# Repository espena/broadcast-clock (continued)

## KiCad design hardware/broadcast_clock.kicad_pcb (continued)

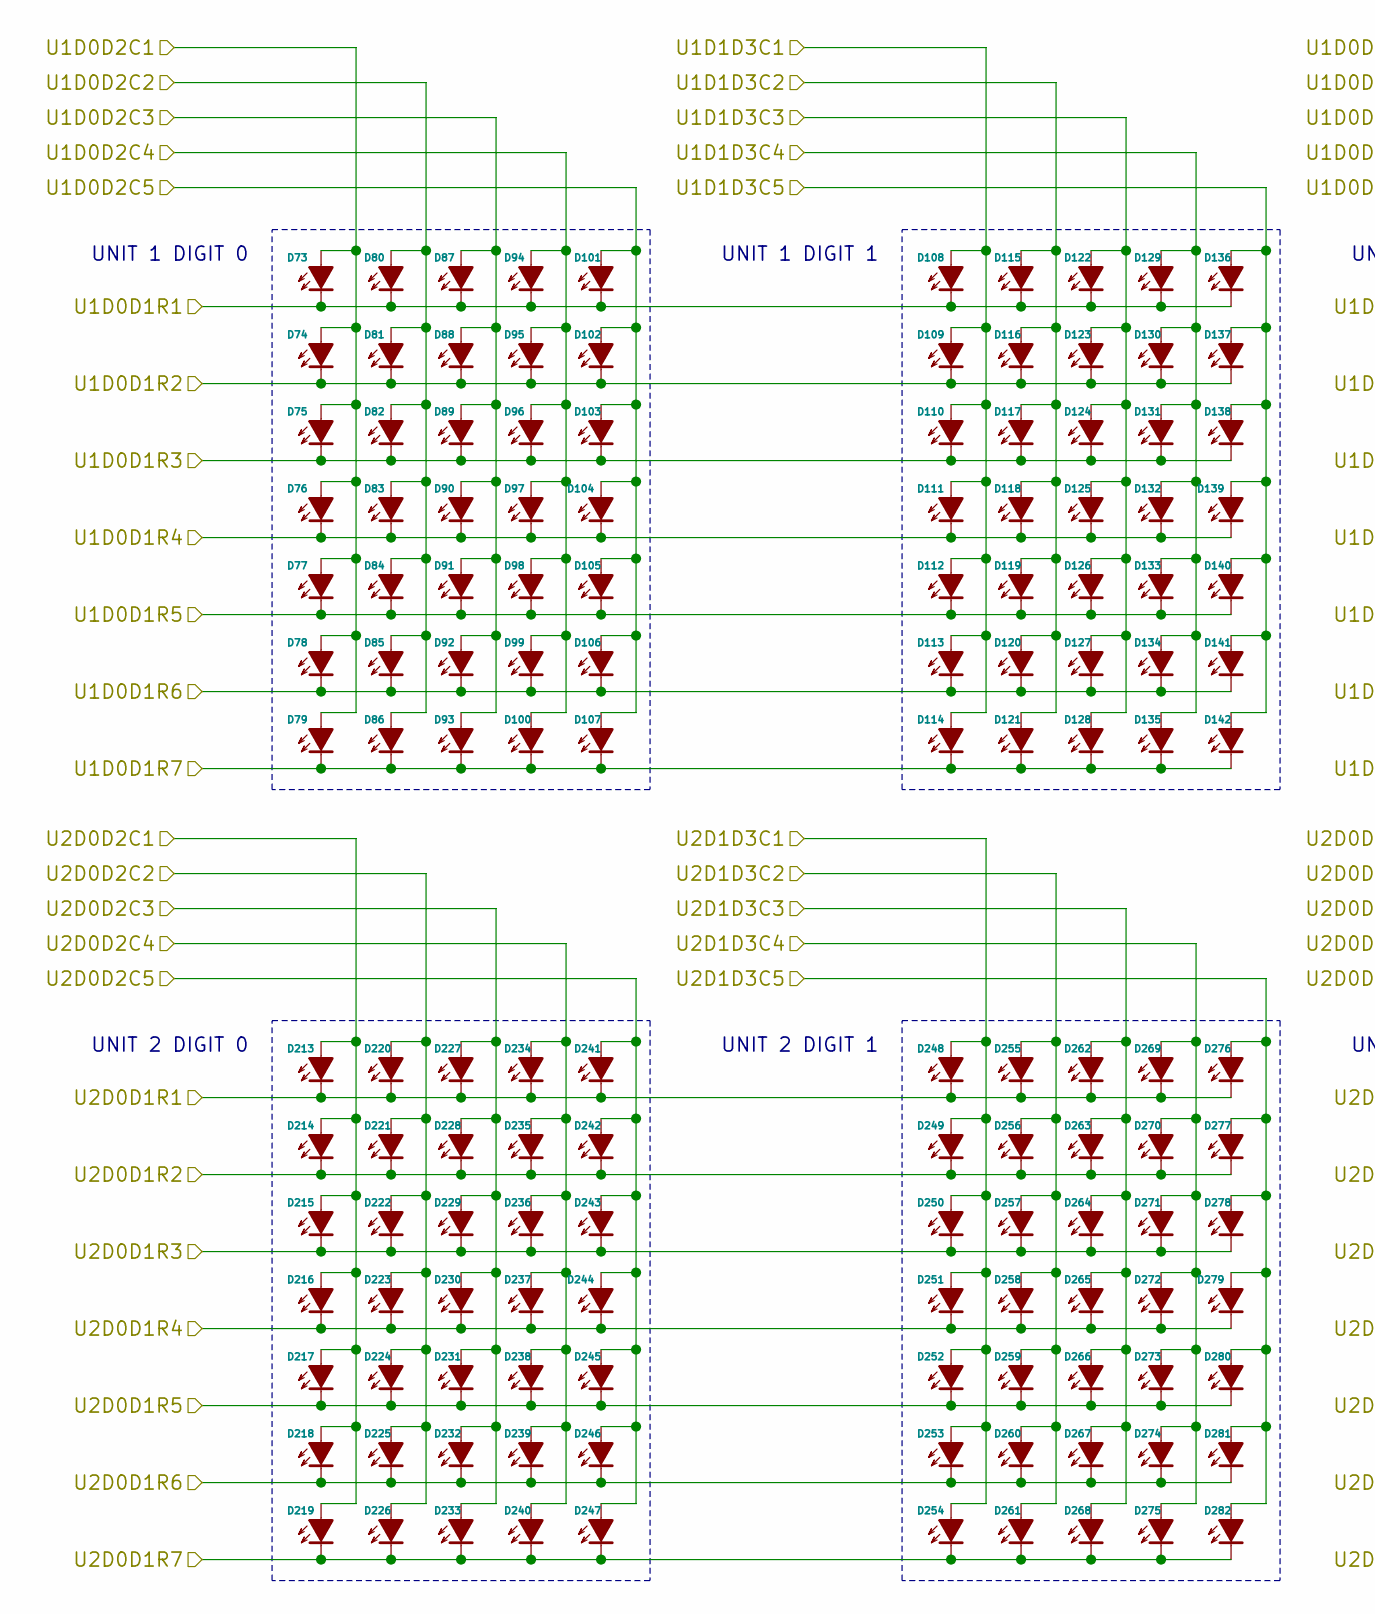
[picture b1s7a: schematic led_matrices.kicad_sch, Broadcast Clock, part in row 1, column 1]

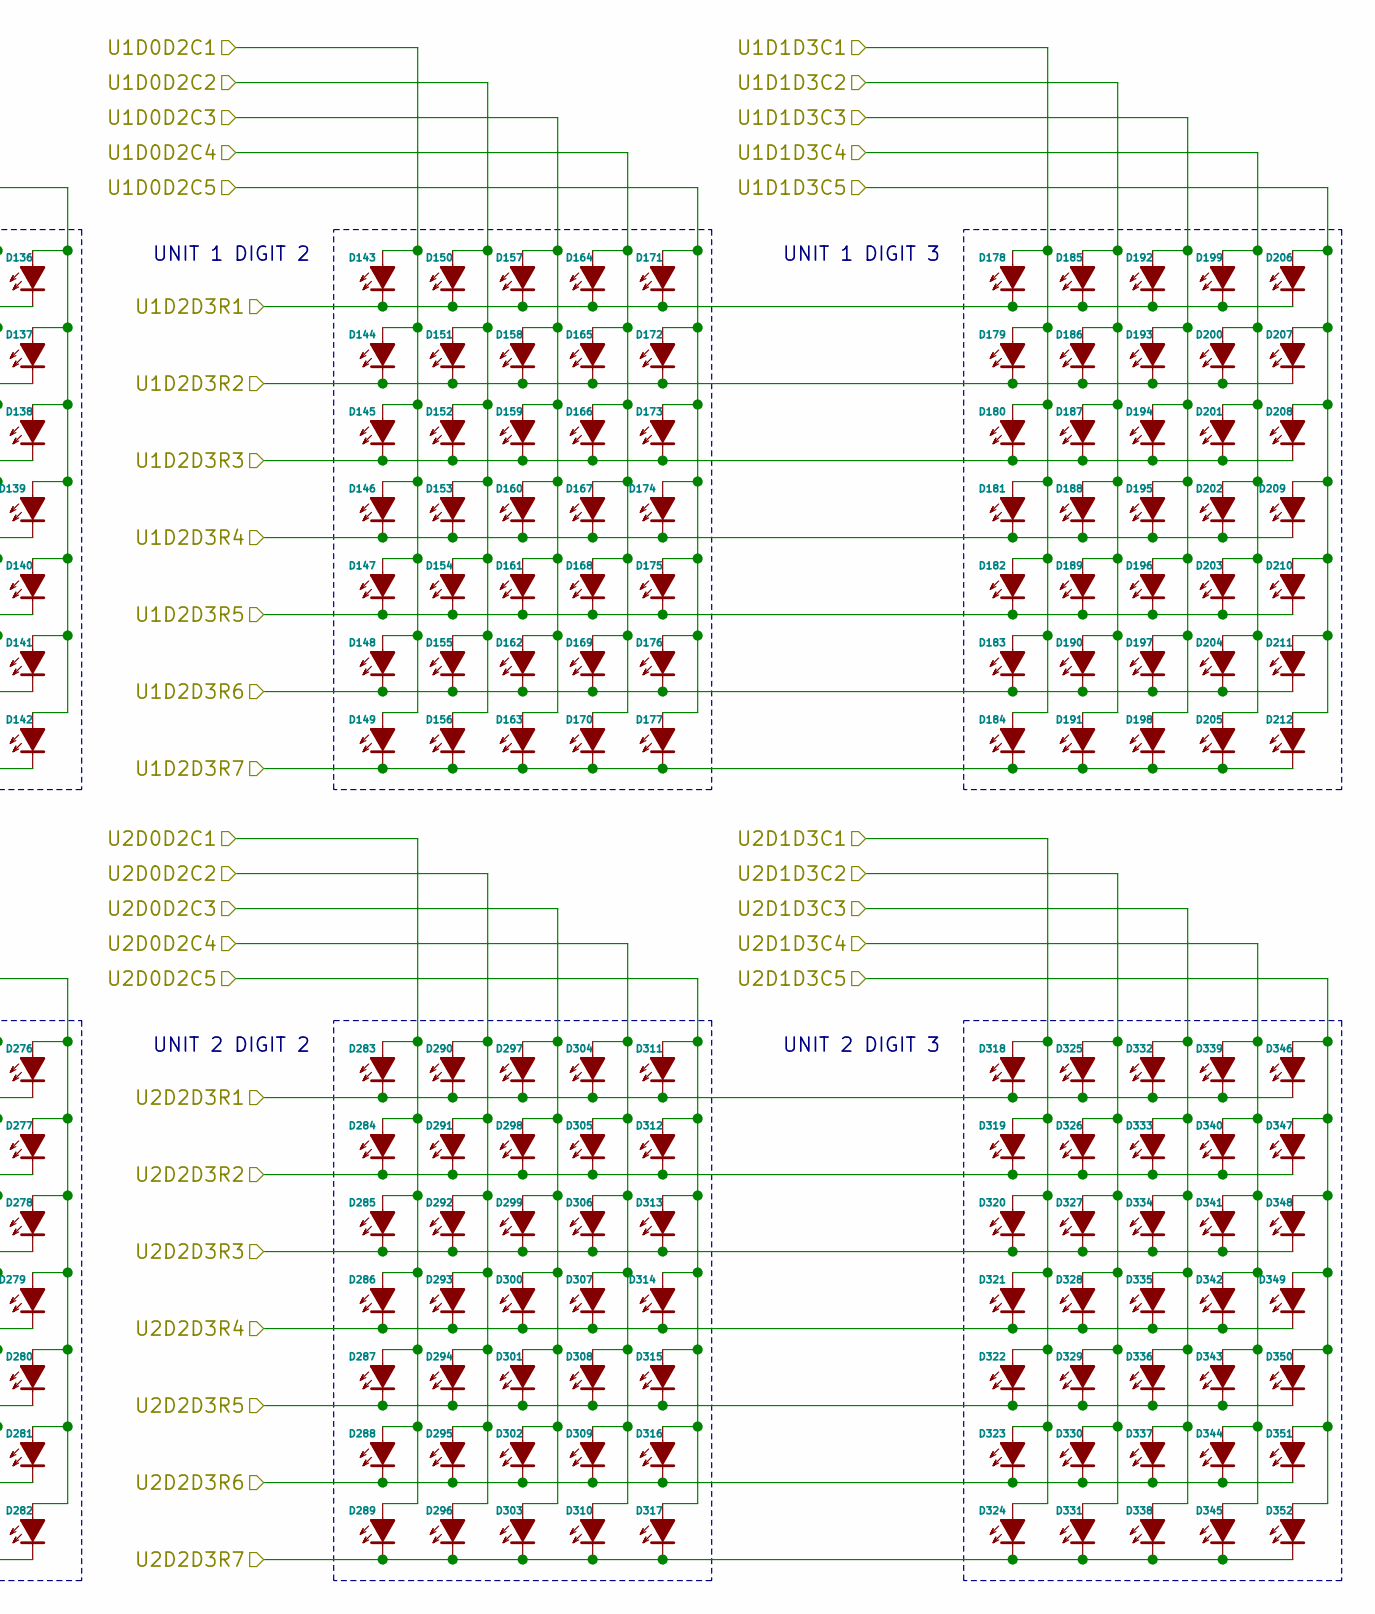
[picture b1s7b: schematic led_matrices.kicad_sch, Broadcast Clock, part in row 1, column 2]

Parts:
D73, D74, D75, D76, D77, D78, D79, D80, D81, D82, D83, D84, D85, D86, D87, D88, D89, D90, D91, D92, D93, D94, D95, D96, D97, D98, D99, D100, D101, D102, D103, D104, D105, D106, D107, D108, D109, D110, D111, D112, D113, D114, D115, D116, D117, D118, D119, D120, D121, D122, D123, D124, D125, D126, D127, D128, D129, D130, D131, D132, D133, D134, D135, D136, D137, D138, D139, D140, D141, D142, D143, D144, D145, D146, D147, D148, D149, D150, D151, D152, D153, D154, D155, D156, D157, D158, D159, D160, D161, D162, D163, D164, D165, D166, D167, D168, D169, D170, D171, D172, D173, D174, D175, D176, D177, D178, D179, D180, D181, D182, D183, D184, D185, D186, D187, D188, D189, D190, D191, D192, D193, D194, D195, D196, D197, D198, D199, D200, D201, D202, D203, D204, D205, D206, D207, D208, D209, D210, D211, D212: 620nm; LED_D5.0mm_p2.54
D213, D214, D215, D216, D217, D218, D219, D220, D221, D222, D223, D224, D225, D226, D227, D228, D229, D230, D231, D232, D233, D234, D235, D236, D237, D238, D239, D240, D241, D242, D243, D244, D245, D246, D247, D248, D249, D250, D251, D252, D253, D254, D255, D256, D257, D258, D259, D260, D261, D262, D263, D264, D265, D266, D267, D268, D269, D270, D271, D272, D273, D274, D275, D276, D277, D278, D279, D280, D281, D282, D283, D284, D285, D286, D287, D288, D289, D290, D291, D292, D293, D294, D295, D296, D297, D298, D299, D300, D301, D302, D303, D304, D305, D306, D307, D308, D309, D310, D311, D312, D313, D314, D315, D316, D317, D318, D319, D320, D321, D322, D323, D324, D325, D326, D327, D328, D329, D330, D331, D332, D333, D334, D335, D336, D337, D338, D339, D340, D341, D342, D343, D344, D345, D346, D347, D348, D349, D350, D351, D352: 620nm; LED_D3.0mm_p2.28

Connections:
/Clock face/LED display/LED matrices/U1D0D1R1: D73.1 (K), D80.1 (K), D87.1 (K), D94.1 (K), D101.1 (K), D108.1 (K), D115.1 (K), D122.1 (K), D129.1 (K), D136.1 (K); also elsewhere on the board
/Clock face/LED display/LED matrices/U1D0D1R2: D74.1 (K), D81.1 (K), D88.1 (K), D95.1 (K), D102.1 (K), D109.1 (K), D116.1 (K), D123.1 (K), D130.1 (K), D137.1 (K); also elsewhere on the board
/Clock face/LED display/LED matrices/U1D0D1R3: D75.1 (K), D82.1 (K), D89.1 (K), D96.1 (K), D103.1 (K), D110.1 (K), D117.1 (K), D124.1 (K), D131.1 (K), D138.1 (K); also elsewhere on the board
/Clock face/LED display/LED matrices/U1D0D1R4: D76.1 (K), D83.1 (K), D90.1 (K), D97.1 (K), D104.1 (K), D111.1 (K), D118.1 (K), D125.1 (K), D132.1 (K), D139.1 (K); also elsewhere on the board
/Clock face/LED display/LED matrices/U1D0D1R5: D77.1 (K), D84.1 (K), D91.1 (K), D98.1 (K), D105.1 (K), D112.1 (K), D119.1 (K), D126.1 (K), D133.1 (K), D140.1 (K); also elsewhere on the board
/Clock face/LED display/LED matrices/U1D0D1R6: D78.1 (K), D85.1 (K), D92.1 (K), D99.1 (K), D106.1 (K), D113.1 (K), D120.1 (K), D127.1 (K), D134.1 (K), D141.1 (K); also elsewhere on the board
/Clock face/LED display/LED matrices/U1D0D1R7: D79.1 (K), D86.1 (K), D93.1 (K), D100.1 (K), D107.1 (K), D114.1 (K), D121.1 (K), D128.1 (K), D135.1 (K), D142.1 (K); also elsewhere on the board
/Clock face/LED display/LED matrices/U1D0D2C1: D73.2 (A), D74.2 (A), D75.2 (A), D76.2 (A), D77.2 (A), D78.2 (A), D79.2 (A), D143.2 (A), D144.2 (A), D145.2 (A), D146.2 (A), D147.2 (A), D148.2 (A), D149.2 (A); also elsewhere on the board
/Clock face/LED display/LED matrices/U1D0D2C2: D80.2 (A), D81.2 (A), D82.2 (A), D83.2 (A), D84.2 (A), D85.2 (A), D86.2 (A), D150.2 (A), D151.2 (A), D152.2 (A), D153.2 (A), D154.2 (A), D155.2 (A), D156.2 (A); also elsewhere on the board
/Clock face/LED display/LED matrices/U1D0D2C3: D87.2 (A), D88.2 (A), D89.2 (A), D90.2 (A), D91.2 (A), D92.2 (A), D93.2 (A), D157.2 (A), D158.2 (A), D159.2 (A), D160.2 (A), D161.2 (A), D162.2 (A), D163.2 (A); also elsewhere on the board
/Clock face/LED display/LED matrices/U1D0D2C4: D94.2 (A), D95.2 (A), D96.2 (A), D97.2 (A), D98.2 (A), D99.2 (A), D100.2 (A), D164.2 (A), D165.2 (A), D166.2 (A), D167.2 (A), D168.2 (A), D169.2 (A), D170.2 (A); also elsewhere on the board
/Clock face/LED display/LED matrices/U1D0D2C5: D101.2 (A), D102.2 (A), D103.2 (A), D104.2 (A), D105.2 (A), D106.2 (A), D107.2 (A), D171.2 (A), D172.2 (A), D173.2 (A), D174.2 (A), D175.2 (A), D176.2 (A), D177.2 (A); also elsewhere on the board
/Clock face/LED display/LED matrices/U1D1D3C1: D108.2 (A), D109.2 (A), D110.2 (A), D111.2 (A), D112.2 (A), D113.2 (A), D114.2 (A), D178.2 (A), D179.2 (A), D180.2 (A), D181.2 (A), D182.2 (A), D183.2 (A), D184.2 (A); also elsewhere on the board
/Clock face/LED display/LED matrices/U1D1D3C2: D115.2 (A), D116.2 (A), D117.2 (A), D118.2 (A), D119.2 (A), D120.2 (A), D121.2 (A), D185.2 (A), D186.2 (A), D187.2 (A), D188.2 (A), D189.2 (A), D190.2 (A), D191.2 (A); also elsewhere on the board
/Clock face/LED display/LED matrices/U1D1D3C3: D122.2 (A), D123.2 (A), D124.2 (A), D125.2 (A), D126.2 (A), D127.2 (A), D128.2 (A), D192.2 (A), D193.2 (A), D194.2 (A), D195.2 (A), D196.2 (A), D197.2 (A), D198.2 (A); also elsewhere on the board
/Clock face/LED display/LED matrices/U1D1D3C4: D129.2 (A), D130.2 (A), D131.2 (A), D132.2 (A), D133.2 (A), D134.2 (A), D135.2 (A), D199.2 (A), D200.2 (A), D201.2 (A), D202.2 (A), D203.2 (A), D204.2 (A), D205.2 (A); also elsewhere on the board
/Clock face/LED display/LED matrices/U1D1D3C5: D136.2 (A), D137.2 (A), D138.2 (A), D139.2 (A), D140.2 (A), D141.2 (A), D142.2 (A), D206.2 (A), D207.2 (A), D208.2 (A), D209.2 (A), D210.2 (A), D211.2 (A), D212.2 (A); also elsewhere on the board
/Clock face/LED display/LED matrices/U1D2D3R1: D143.1 (K), D150.1 (K), D157.1 (K), D164.1 (K), D171.1 (K), D178.1 (K), D185.1 (K), D192.1 (K), D199.1 (K), D206.1 (K); also elsewhere on the board
/Clock face/LED display/LED matrices/U1D2D3R2: D144.1 (K), D151.1 (K), D158.1 (K), D165.1 (K), D172.1 (K), D179.1 (K), D186.1 (K), D193.1 (K), D200.1 (K), D207.1 (K); also elsewhere on the board
/Clock face/LED display/LED matrices/U1D2D3R3: D145.1 (K), D152.1 (K), D159.1 (K), D166.1 (K), D173.1 (K), D180.1 (K), D187.1 (K), D194.1 (K), D201.1 (K), D208.1 (K); also elsewhere on the board
/Clock face/LED display/LED matrices/U1D2D3R4: D146.1 (K), D153.1 (K), D160.1 (K), D167.1 (K), D174.1 (K), D181.1 (K), D188.1 (K), D195.1 (K), D202.1 (K), D209.1 (K); also elsewhere on the board
/Clock face/LED display/LED matrices/U1D2D3R5: D147.1 (K), D154.1 (K), D161.1 (K), D168.1 (K), D175.1 (K), D182.1 (K), D189.1 (K), D196.1 (K), D203.1 (K), D210.1 (K); also elsewhere on the board
/Clock face/LED display/LED matrices/U1D2D3R6: D148.1 (K), D155.1 (K), D162.1 (K), D169.1 (K), D176.1 (K), D183.1 (K), D190.1 (K), D197.1 (K), D204.1 (K), D211.1 (K); also elsewhere on the board
/Clock face/LED display/LED matrices/U1D2D3R7: D149.1 (K), D156.1 (K), D163.1 (K), D170.1 (K), D177.1 (K), D184.1 (K), D191.1 (K), D198.1 (K), D205.1 (K), D212.1 (K); also elsewhere on the board
/Clock face/LED display/LED matrices/U2D0D1R1: D213.1 (K), D220.1 (K), D227.1 (K), D234.1 (K), D241.1 (K), D248.1 (K), D255.1 (K), D262.1 (K), D269.1 (K), D276.1 (K); also elsewhere on the board
/Clock face/LED display/LED matrices/U2D0D1R2: D214.1 (K), D221.1 (K), D228.1 (K), D235.1 (K), D242.1 (K), D249.1 (K), D256.1 (K), D263.1 (K), D270.1 (K), D277.1 (K); also elsewhere on the board
/Clock face/LED display/LED matrices/U2D0D1R3: D215.1 (K), D222.1 (K), D229.1 (K), D236.1 (K), D243.1 (K), D250.1 (K), D257.1 (K), D264.1 (K), D271.1 (K), D278.1 (K); also elsewhere on the board
/Clock face/LED display/LED matrices/U2D0D1R4: D216.1 (K), D223.1 (K), D230.1 (K), D237.1 (K), D244.1 (K), D251.1 (K), D258.1 (K), D265.1 (K), D272.1 (K), D279.1 (K); also elsewhere on the board
/Clock face/LED display/LED matrices/U2D0D1R5: D217.1 (K), D224.1 (K), D231.1 (K), D238.1 (K), D245.1 (K), D252.1 (K), D259.1 (K), D266.1 (K), D273.1 (K), D280.1 (K); also elsewhere on the board
/Clock face/LED display/LED matrices/U2D0D1R6: D218.1 (K), D225.1 (K), D232.1 (K), D239.1 (K), D246.1 (K), D253.1 (K), D260.1 (K), D267.1 (K), D274.1 (K), D281.1 (K); also elsewhere on the board
/Clock face/LED display/LED matrices/U2D0D1R7: D219.1 (K), D226.1 (K), D233.1 (K), D240.1 (K), D247.1 (K), D254.1 (K), D261.1 (K), D268.1 (K), D275.1 (K), D282.1 (K); also elsewhere on the board
/Clock face/LED display/LED matrices/U2D0D2C1: D213.2 (A), D214.2 (A), D215.2 (A), D216.2 (A), D217.2 (A), D218.2 (A), D219.2 (A), D283.2 (A), D284.2 (A), D285.2 (A), D286.2 (A), D287.2 (A), D288.2 (A), D289.2 (A); also elsewhere on the board
/Clock face/LED display/LED matrices/U2D0D2C2: D220.2 (A), D221.2 (A), D222.2 (A), D223.2 (A), D224.2 (A), D225.2 (A), D226.2 (A), D290.2 (A), D291.2 (A), D292.2 (A), D293.2 (A), D294.2 (A), D295.2 (A), D296.2 (A); also elsewhere on the board
/Clock face/LED display/LED matrices/U2D0D2C3: D227.2 (A), D228.2 (A), D229.2 (A), D230.2 (A), D231.2 (A), D232.2 (A), D233.2 (A), D297.2 (A), D298.2 (A), D299.2 (A), D300.2 (A), D301.2 (A), D302.2 (A), D303.2 (A); also elsewhere on the board
/Clock face/LED display/LED matrices/U2D0D2C4: D234.2 (A), D235.2 (A), D236.2 (A), D237.2 (A), D238.2 (A), D239.2 (A), D240.2 (A), D304.2 (A), D305.2 (A), D306.2 (A), D307.2 (A), D308.2 (A), D309.2 (A), D310.2 (A); also elsewhere on the board
/Clock face/LED display/LED matrices/U2D0D2C5: D241.2 (A), D242.2 (A), D243.2 (A), D244.2 (A), D245.2 (A), D246.2 (A), D247.2 (A), D311.2 (A), D312.2 (A), D313.2 (A), D314.2 (A), D315.2 (A), D316.2 (A), D317.2 (A); also elsewhere on the board
/Clock face/LED display/LED matrices/U2D1D3C1: D248.2 (A), D249.2 (A), D250.2 (A), D251.2 (A), D252.2 (A), D253.2 (A), D254.2 (A), D318.2 (A), D319.2 (A), D320.2 (A), D321.2 (A), D322.2 (A), D323.2 (A), D324.2 (A); also elsewhere on the board
/Clock face/LED display/LED matrices/U2D1D3C2: D255.2 (A), D256.2 (A), D257.2 (A), D258.2 (A), D259.2 (A), D260.2 (A), D261.2 (A), D325.2 (A), D326.2 (A), D327.2 (A), D328.2 (A), D329.2 (A), D330.2 (A), D331.2 (A); also elsewhere on the board
/Clock face/LED display/LED matrices/U2D1D3C3: D262.2 (A), D263.2 (A), D264.2 (A), D265.2 (A), D266.2 (A), D267.2 (A), D268.2 (A), D332.2 (A), D333.2 (A), D334.2 (A), D335.2 (A), D336.2 (A), D337.2 (A), D338.2 (A); also elsewhere on the board
/Clock face/LED display/LED matrices/U2D1D3C4: D269.2 (A), D270.2 (A), D271.2 (A), D272.2 (A), D273.2 (A), D274.2 (A), D275.2 (A), D339.2 (A), D340.2 (A), D341.2 (A), D342.2 (A), D343.2 (A), D344.2 (A), D345.2 (A); also elsewhere on the board
/Clock face/LED display/LED matrices/U2D1D3C5: D276.2 (A), D277.2 (A), D278.2 (A), D279.2 (A), D280.2 (A), D281.2 (A), D282.2 (A), D346.2 (A), D347.2 (A), D348.2 (A), D349.2 (A), D350.2 (A), D351.2 (A), D352.2 (A); also elsewhere on the board
/Clock face/LED display/LED matrices/U2D2D3R1: D283.1 (K), D290.1 (K), D297.1 (K), D304.1 (K), D311.1 (K), D318.1 (K), D325.1 (K), D332.1 (K), D339.1 (K), D346.1 (K); also elsewhere on the board
/Clock face/LED display/LED matrices/U2D2D3R2: D284.1 (K), D291.1 (K), D298.1 (K), D305.1 (K), D312.1 (K), D319.1 (K), D326.1 (K), D333.1 (K), D340.1 (K), D347.1 (K); also elsewhere on the board
/Clock face/LED display/LED matrices/U2D2D3R3: D285.1 (K), D292.1 (K), D299.1 (K), D306.1 (K), D313.1 (K), D320.1 (K), D327.1 (K), D334.1 (K), D341.1 (K), D348.1 (K); also elsewhere on the board
/Clock face/LED display/LED matrices/U2D2D3R4: D286.1 (K), D293.1 (K), D300.1 (K), D307.1 (K), D314.1 (K), D321.1 (K), D328.1 (K), D335.1 (K), D342.1 (K), D349.1 (K); also elsewhere on the board
/Clock face/LED display/LED matrices/U2D2D3R5: D287.1 (K), D294.1 (K), D301.1 (K), D308.1 (K), D315.1 (K), D322.1 (K), D329.1 (K), D336.1 (K), D343.1 (K), D350.1 (K); also elsewhere on the board
/Clock face/LED display/LED matrices/U2D2D3R6: D288.1 (K), D295.1 (K), D302.1 (K), D309.1 (K), D316.1 (K), D323.1 (K), D330.1 (K), D337.1 (K), D344.1 (K), D351.1 (K); also elsewhere on the board
/Clock face/LED display/LED matrices/U2D2D3R7: D289.1 (K), D296.1 (K), D303.1 (K), D310.1 (K), D317.1 (K), D324.1 (K), D331.1 (K), D338.1 (K), D345.1 (K), D352.1 (K); also elsewhere on the board

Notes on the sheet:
UNIT 2 DIGIT 2
UNIT 2 DIGIT 0
UNIT 1 DIGIT 0
UNIT 2 DIGIT 1
UNIT 2 DIGIT 3
UNIT 1 DIGIT 1
UNIT 1 DIGIT 3
UNIT 1 DIGIT 2

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
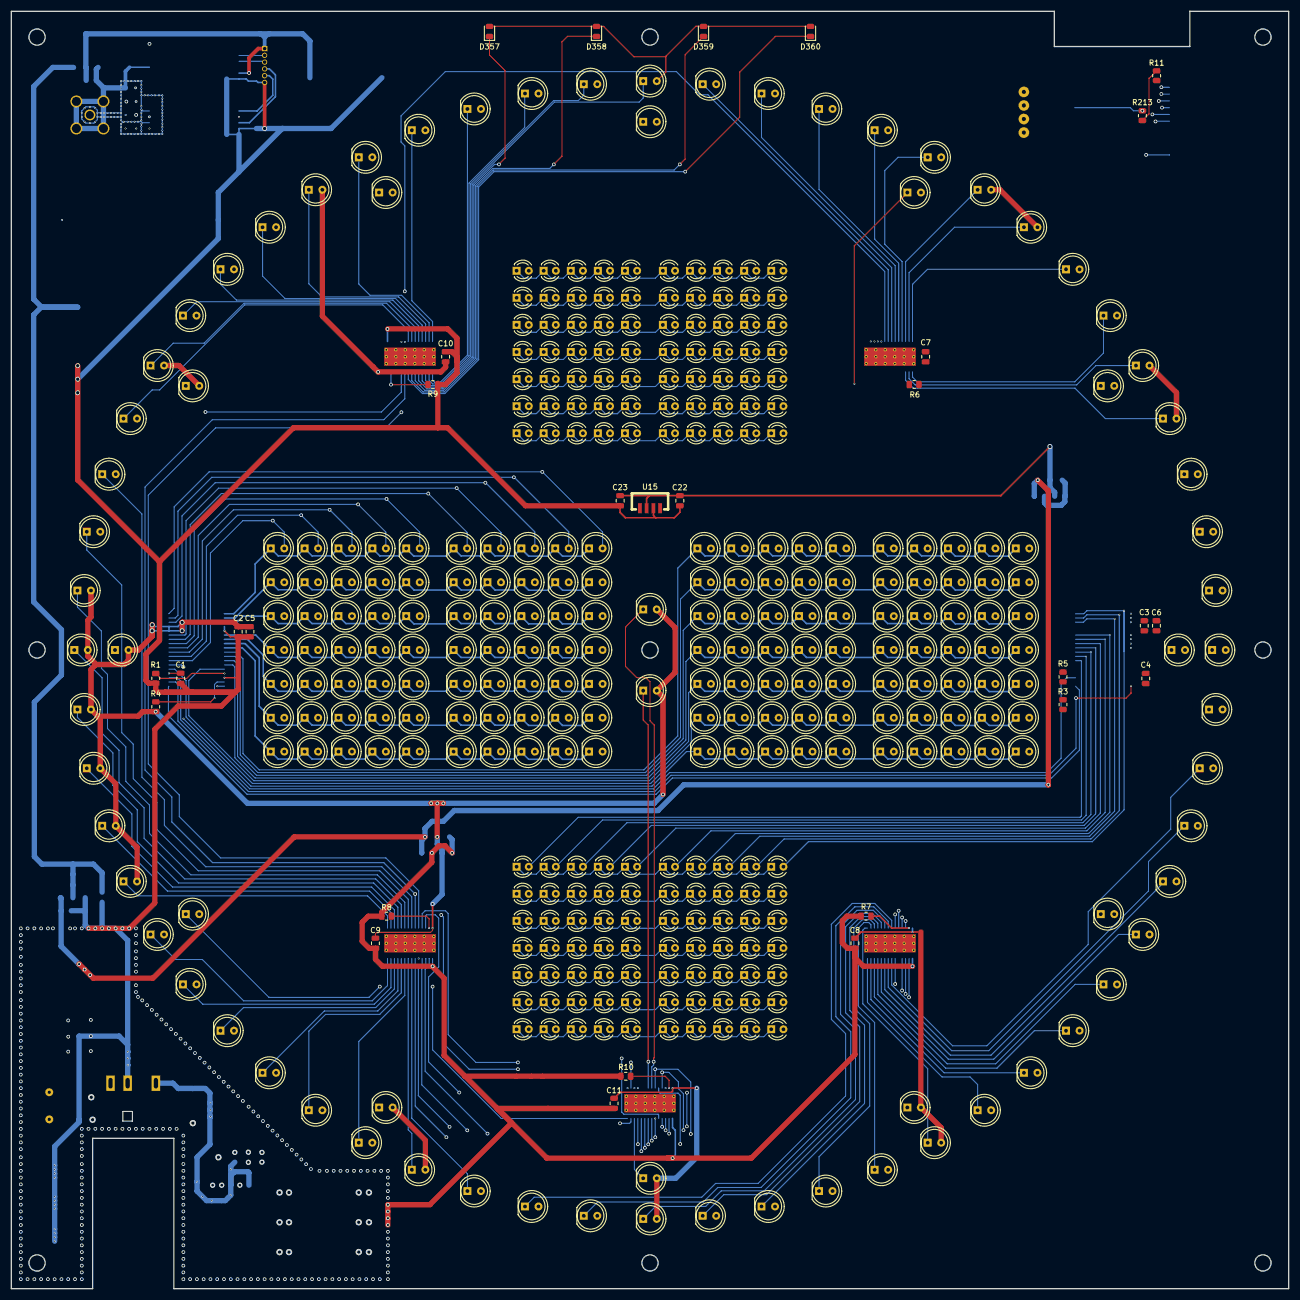
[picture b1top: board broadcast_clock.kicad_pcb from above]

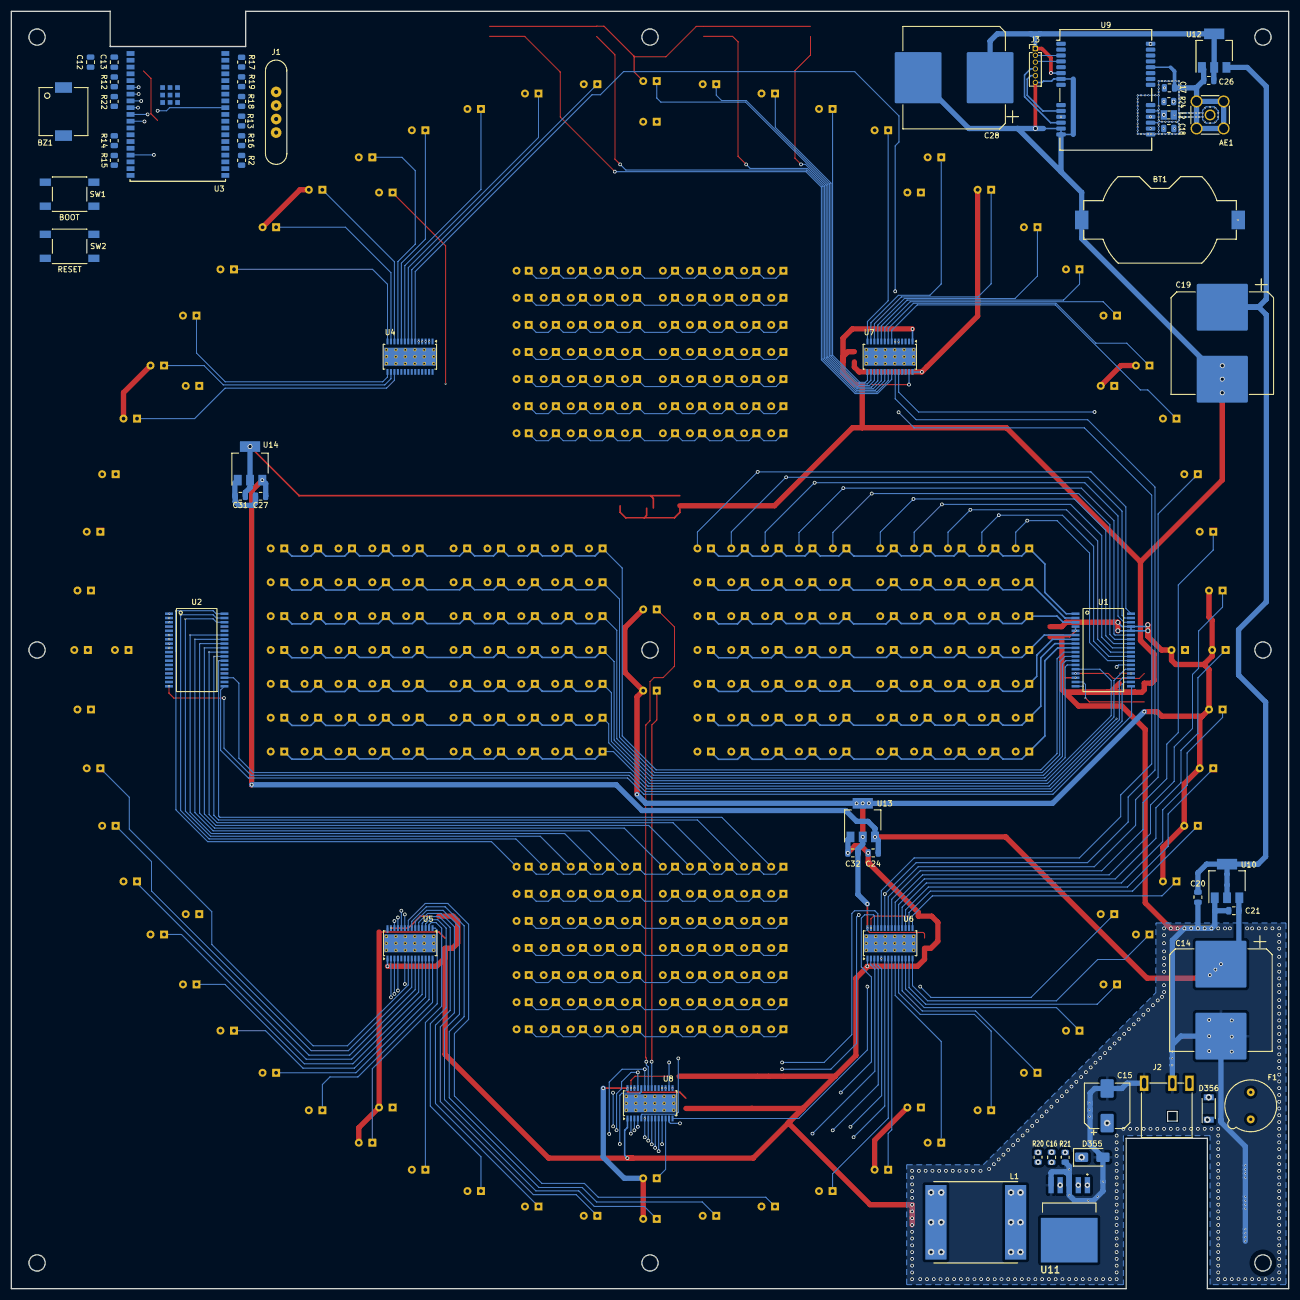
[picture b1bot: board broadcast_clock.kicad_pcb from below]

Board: 4 copper layers, 239.5 x 239.5 mm, 439 parts (56 on the bottom side), 184 nets.

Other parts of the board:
C13: 47uF; C_0805_2012Metric
C22: 100nF; C_0805_2012Metric
C23: 10μF; C_0805_2012Metric
R22: 10k; R_0805_2012Metric

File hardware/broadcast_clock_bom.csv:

"Reference","Value","Datasheet","Footprint","Qty","DNP"
"AE1","Active GPS antenna 3.3V","~","Connector_Coaxial:SMA_Amphenol_132291-12_Vertical","1",""
"BT1","CR 2032","~","Battery:BatteryHolder_Keystone_1058_1x2032","1",""
"BZ1","Buzzer","~","Transducer_espena:TP094003_Transducer_9x9mm","1",""
"C1,C4","26pF","~","Capacitor_SMD:C_0805_2012Metric","2",""
"C2,C3,C7,C8,C9,C10,C11,C20,C22,C26,C31,C32","100nF","~","Capacitor_SMD:C_0805_2012Metric","12",""
"C5,C6,C13","47uF","~","Capacitor_SMD:C_0805_2012Metric","3",""
"C12","1uF","~","Capacitor_SMD:C_0805_2012Metric","1",""
"C14,C19,C28","820uF","~","Capacitor_SMD_espena:CP_Elec_18x16.5","3",""
"C15,C25","100uF","~","Capacitor_SMD:CP_Elec_8x10","2",""
"C16","40nF","~","Capacitor_SMD:C_0805_2012Metric","1",""
"C17","10nF","~","Capacitor_SMD:C_0805_2012Metric","1",""
"C18","47pF","~","Capacitor_SMD:C_0805_2012Metric","1",""
"C21,C24,C27","10µF","~","Capacitor_SMD:C_0805_2012Metric","3",""
"C23","10μF","~","Capacitor_SMD:C_0805_2012Metric","1",""
"D1,D2,D3,D4,D5,D6,D7,D8,D9,D10,D11,D12,D13,D14,D15,D16,D17,D18,D19,D20,D21,D22,D23,D24,D25,D26,D27,D28,D29,D30,D31,D32,D33,D34,D35,D36,D37,D38,D39,D40,D41,D42,D43,D44,D45,D46,D47,D48,D49,D50,D51,D52,D53,D54,D55,D56,D57,D58,D59,D60,D61,D62,D63,D64,D65,D66,D67,D68,D69,D70,D71,D72,D73,D74,D75,D76,D77,D78,D79,D80,D81,D82,D83,D84,D85,D86,D87,D88,D89,D90,D91,D92,D93,D94,D95,D96,D97,D98,D99,D100,D101,D102,D103,D104,D105,D106,D107,D108,D109,D110,D111,D112,D113,D114,D115,D116,D117,D118,D119,D120,D121,D122,D123,D124,D125,D126,D127,D128,D129,D130,D131,D132,D133,D134,D135,D136,D137,D138,D139,D140,D141,D142,D143,D144,D145,D146,D147,D148,D149,D150,D151,D152,D153,D154,D155,D156,D157,D158,D159,D160,D161,D162,D163,D164,D165,D166,D167,D168,D169,D170,D171,D172,D173,D174,D175,D176,D177,D178,D179,D180,D181,D182,D183,D184,D185,D186,D187,D188,D189,D190,D191,D192,D193,D194,D195,D196,D197,D198,D199,D200,D201,D202,D203,D204,D205,D206,D207,D208,D209,D210,D211,D212,D213,D214,D215,D216,D217,D218,D219,D220,D221,D222,D223,D224,D225,D226,D227,D228,D229,D230,D231,D232,D233,D234,D235,D236,D237,D238,D239,D240,D241,D242,D243,D244,D245,D246,D247,D248,D249,D250,D251,D252,D253,D254,D255,D256,D257,D258,D259,D260,D261,D262,D263,D264,D265,D266,D267,D268,D269,D270,D271,D272,D273,D274,D275,D276,D277,D278,D279,D280,D281,D282,D283,D284,D285,D286,D287,D288,D289,D290,D291,D292,D293,D294,D295,D296,D297,D298,D299,D300,D301,D302,D303,D304,D305,D306,D307,D308,D309,D310,D311,D312,D313,D314,D315,D316,D317,D318,D319,D320,D321,D322,D323,D324,D325,D326,D327,D328,D329,D330,D331,D332,D333,D334,D335,D336,D337,D338,D339,D340,D341,D342,D343,D344,D345,D346,D347,D348,D349,D350,D351,D352,D353,D354,D360","620nm","~","-- mixed values --","355",""
"D355","SK33","~","Diode_SMD:D_SMA","1",""
"D356","CMS04","~","Diode_SMD_mouser:SODFL4724X108N","1",""
"D357","470nm","~","LED_SMD:LED_0805_2012Metric","1",""
"D358","570nm","~","LED_SMD:LED_0805_2012Metric","1",""
"D359","590nm","~","LED_SMD:LED_0805_2012Metric","1",""
"F1","2A","~","Fuse_espena:FuseHolder_Keystone_3554","1",""
"J1","UART MCU","~","Connector_espena:Magnetic-Pogo-Female-MG0425FB_1x4_P2.54mm","1",""
"J2","POWER","~","Connector_BarrelJack_espena:BarrelJack_DC044_Horizontal","1",""
"J3","UART GPS","~","Connector_PinHeader_1.27mm:PinHeader_1x06_P1.27mm_Vertical","1",""
"L1","37uH","~","Inductor_SMD_espena:L_Pulse_LCI-44","1",""
"L2","27nH","~","Inductor_SMD_espena:L_Coilcraft_0805CS","1",""
"R1,R5","53.6k","~","Resistor_SMD:R_0805_2012Metric","2",""
"R2,R3,R13","4.7k","~","Resistor_SMD:R_0805_2012Metric","3",""
"R4,R11","R","~","Resistor_SMD:R_0805_2012Metric","2",""
"R6,R7,R8,R9,R10","2k","~","Resistor_SMD:R_0805_2012Metric","5",""
"R12","4,7k","~","Resistor_SMD:R_0805_2012Metric","1",""
"R14,R16,R22,R213","10k","~","Resistor_SMD:R_0805_2012Metric","4",""
"R15","10k","~","Resistor_SMD:R_0805_2012Metric","1","DNP"
"R17,R18","4k7","~","Resistor_SMD:R_0805_2012Metric","2","DNP"
"R19","4k7","~","Resistor_SMD:R_0805_2012Metric","1",""
"R20","5.6kΩ","~","Resistor_SMD:R_0805_2012Metric","1",""
"R21","1kΩ","~","Resistor_SMD:R_0805_2012Metric","1",""
"R24","10Ω","~","Resistor_SMD:R_0805_2012Metric","1",""
"SW1","BOOT","~","Button_Switch_SMD_espena:SW_SPST_TL3301_6x6mm_H4.3mm","1",""
"SW2","RESET","~","Button_Switch_SMD_espena:SW_SPST_TL3301_6x6mm_H4.3mm","1",""
"U1,U2","MAX6952","https://www.analog.com/MAX6952/datasheet","Package_SO_espena:SSOP-36_7.5x12.5mm_P0.65mm","2",""
"U3","ESP32-WROVER-E","https://www.espressif.com/sites/default/files/documentation/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","RF_Module_espena:ESP32-WROVER-B","1",""
"U4,U5,U6,U7,U8","TLC5940PWP","http://www.ti.com/lit/ds/symlink/tlc5940.pdf","Package_SO:HTSSOP-28-1EP_4.4x9.7mm_P0.65mm_EP3.4x9.5mm_Mask2.4x6.17mm_ThermalVias","5",""
"U9","LEA-M8T","https://content.u-blox.com/sites/default/files/documents/NEO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","RF_GPS_espena:ublox_LEA","1",""
"U10","NCP1117-5.0","http://www.onsemi.com/pub_link/Collateral/NCP1117-D.PDF","Package_TO_SOT_SMD:SOT-223-3_TabPin2","1",""
"U11","LM2596DS-ADJ","http://www.ti.com/lit/ds/symlink/lm2596.pdf","Regulator_SMD_mouser:NCP5663DSADJR4G","1",""
"U12,U13,U14","NCP1117-3.3","http://www.onsemi.com/pub_link/Collateral/NCP1117-D.PDF","Package_TO_SOT_SMD:SOT-223-3_TabPin2","3",""
"U15","VEML7700","https://www.vishay.com/docs/84286/veml7700.pdf","Sensor_espena:VEML7700","1",""

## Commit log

2024-05-11 Rename KiCAD folder
2024-05-11 Remove backup files from repo
2024-05-11 Do not put future backup files in repo
2024-05-11 Nuke DS_Store
2024-05-11 Proper title
2024-05-11 Title casing
2024-05-11 Remove .DS_Store
2024-05-12 Add 3D rendering from KiCAD
2024-05-12 Assign footprints
2024-05-12 Omit cache file
2024-05-12 Correct typo
2024-05-12 Remove subtitle
2024-05-12 Insert vertical spacing
2024-05-26 Starting PCB routing process
2024-05-28 Routing in progress
2024-06-01 Adding thermal zones
2024-06-01 Zone fills completed
2024-06-05 Add graphics
2024-06-05 Open thermal pad for buck converter
2024-06-05 Open thermal pad for buck converter
    Former-commit-id: e6c8dc76280dd95d3ab8586baa877e8ee88db5e2
2024-07-05 Prototype, starting on firmware
    Former-commit-id: 3c22e4f94bda4a4eed472ac1ff762e7709731c05
    Former-commit-id: afce4fecf5b4961621dea2f3a514203675ae8e80
2024-07-05 Ignore large files and build dirs
    Former-commit-id: 0e18799fed59ba45a7fd428bbaa720c14ba5a569
    Former-commit-id: 71ca205f5496226061a88598e82ce050830e1e5e
2024-07-05 Delete build directory
    Former-commit-id: dbb7b6340974d6a32a26e2f38989c59345d58b2c
    Former-commit-id: 0e2b5f06938d1fb80ac796f70e5a84a68d133723
2024-07-05 Remove large 3D files
    Former-commit-id: fe92c8cc630f44c9ad765bc8c56d44807531d97d
    Former-commit-id: 5229d8a8b0247ce2fddd517664bf60847fdd22d5
    Former-commit-id: 9a5f131d8090c7a510589660489c359ea0d1adff
2024-07-05 Remove large file
    Former-commit-id: 858400992d27a81aa4d4257c3e3b97e62c47a14c
    Former-commit-id: cf6a2bc28083189ee85c500fd2892ced109e4cb9
2024-07-05 Remove backups from repo
    Former-commit-id: ee39ae30396c5e1d3ea39ad56737bf511b44934d
2024-07-05 Remove Blender files from repo
    Former-commit-id: e2cc7ec13bb03d01c07dcc691a6b017e271ddb04
2024-07-05 Ignore blender files in the future
    Former-commit-id: 38bdcb28527561a49dea2069897890aafba9dfc2
2024-07-05 Redundant file
    Former-commit-id: 6b6626210259a1440a8c9480d30818385869bb33
2024-07-05 Correct path to IDF build dir
    Former-commit-id: 807dce2e7a5d83d5ca797a04c207875345626c89
2024-07-05 Add init() methods to components
    Former-commit-id: 09d56ffbd4ccf9224b7b9521242767fbbf57e32b
2024-07-06 Firmware for LED drivers, dial and matrix
    Former-commit-id: d06b369f7cd35a3c902f0729a1b8d2d05c7c9555
2024-07-06 Adding WiFi and NTP client
    Former-commit-id: 6913d4e9ed0c89882ef5d993f4d2800f05a9f367
2024-07-06 Add secrets file (temporary storage of credentials)
    Former-commit-id: c86b42d62740096ba66555efd07998bc7e82be6d
2024-07-08 Adding inner frame moutning holes
    Former-commit-id: 4f5b56c85d6e0a8106ced6b64ecd934ffc52be82
2024-07-08 Adding driver for ambient light sensor
    Former-commit-id: 2bce65af87f10816012582e2dad0f4f90b30a819
2024-07-10 Fix display lags, implement brightness adjustment
    Former-commit-id: 36ce102e70e0466296d428186528265a70c2a012
2024-07-10 Change featured image
    Former-commit-id: 8c84f7cc84d50c5ac0d42f407fa92094baa080c8
2024-07-10 Fix error in ignore file
    Former-commit-id: a412ba2b5354aca739f623c65e8a8bf6b69a3bc8
2024-07-10 Do not initialize dial before NTP sync complete
    Former-commit-id: 5a23c4782ce2f07c023ede547e2d34bd3717045c
2024-07-10 Add reference to where to find the clock enclusure.
2024-07-10 Implement WiFi AP with configuration mode
2024-07-11 Fix bug causing unintentionally entering config mode
2024-07-11 Adding 'init mode' for startup condition
2024-07-11 Add delay after setting BLANK line high on update start
2024-07-11 Adding captive portal for configuration mode
2024-07-12 Adding HTTP server and embedding HTML markup for control panel
2024-07-13 Fixed serial communication with the 5940 chips
2024-07-13 Fix HTML config page
2024-07-14 Change include guards to match rest of project
2024-07-14 Adding a (JSON) app configuration wrapper
2024-07-14 Stop debug printing of current light level
2024-07-14 Align light levels with dot matrix
2024-07-14 Align light levels with dial
2024-07-14 Implement simple, tabbed control panel in plain HTML/CSS
2024-07-14 Ignore KiCAD temporary files
2024-07-14 Remove empty CSS rule
2024-07-14 Passing configuration events to event loop
2024-07-14 Reading and writing config from/to NVS
2024-07-15 Implementing configuration settings
2024-07-15 Display exit page after form submission
2024-07-15 Implement 12h time format
2024-07-15 Add getter for integers to configuration class
2024-07-15 Implement auto/fixed brightness control
2024-07-15 Add option to keep configurator available in station mode
2024-07-16 Fix bugs in configurator and remember current tab on reload
2024-07-16 Logical OR operator don't work with template system, use ?? operator for a workaround
2024-07-16 Fix bug in clock mode probing
2024-07-16 Adjust hole sizes
2024-07-16 CNC file
2024-07-16 Use '/save' as action URL and redirect back to '/'
2024-07-16 Update mounting holes, create toolpath for milling
2024-07-16 Fix bug in displaying meridiem (AM/PM)
2024-07-16 Remove 'Save' and 'Exit' notifications
2024-07-18 Implement stop watch
2024-07-18 Slightly adjust buttons position
2024-07-19 Let brightest display mode kick in earlier
2024-07-19 Start implement countdown timer
2024-07-19 Show midnight/midday as 12 and not 00 when in 12h mode
2024-07-19 Add GUI for countdown timer
2024-07-19 Adding info about timers
2024-07-19 Reduce update flickering
2024-07-19 Countdown partially implemented
2024-07-21 Adding beeper for alarms, IP display at boot and do away with flickering
2024-07-21 Fix NTP status indicators
2024-07-23 Refactor dial interface to TLC5940, remove PWM and timers, use loops while keeping WDT in leash
2024-07-23 Rename 'ambient sensor' timer name, it is now doing several things
2024-07-23 Update back panel drawing, add measurements
2024-07-23 Configuration object triggers event on update to enable on-the-fly changes of settings
2024-07-23 Pass event loop handle to configuration object
2024-07-23 Renamed methods
2024-07-23 Fix bug in clock refresh cycle
2024-07-23 Adding favicon.ico to web configurator response
2024-07-26 Update schematics
2024-07-27 Create LICENSE
2024-08-02 Update README.md
    Add link to home site
2024-08-03 Inhibit blinking of indicators
2024-08-03 Adjust brightness level
2024-08-03 Change capacitor value from 26 to 27 pF which is a standard value
2024-08-03 Change fuse from 2A to 250 mA
2024-08-03 Display pcb related layers only
2024-08-03 Add bill of material
2024-08-04 Move bill of material into hardware directory
2024-08-06 Remove R19, pull-up disturbs serial communication
2024-08-08 Minor design updates
2024-08-14 Firmware support for LEA M8T satellite receiver
2024-08-14 Add display test mode
2024-09-17 Implementing support for u-blox LEA M8T
2024-09-18 Satellite clock sync OK, adding status indicators
2024-09-21 Downgrade to previous version of the i2c driver
2024-09-22 Prepare JSON status object
2024-09-24 Create JSON feed for status report
2024-09-24 Fix survey-in GUI
2024-09-25 Set i2c clock speed back to 400K
2024-09-25 Fix spelling error in time mode string
2024-09-28 Fix UI for starting and stopping survey-in
2024-09-28 Add blinking status indicators
2024-10-01 Expand to 16 MB flash memory
2024-10-05 Moved memory allocation to SPI RAM for lea_m8t messages
2024-10-05 Update data at every refresh interval
2024-10-05 Ignore debug data
2024-10-10 GNSS clock sync stable
2024-10-12 Move event listener for timepulse presence into clock_status class
2024-10-12 Fix timepulse absence detection
2024-10-12 Red LED is now blinking on lower accuracy
2024-10-12 Remove redundant files
2024-10-12 Add NTP server boilerplate
2024-10-13 Protect access to system clock with a mutex.
2024-10-13 Wrap time pulse timing in a critical section
2024-10-13 Release systime mutex before triggering UBX_NAV_TIMEUTC event.
2024-10-13 Task priority balancing.
2024-10-13 Implement NTP server.
2024-10-13 NTP server status indicators and control panel.
2024-10-14 Re-implement ambient light sensor
2024-10-15 Refactor: Rename captive_portal_http to http_server
2024-10-19 Add SSID list to UI
2024-10-19 Limit reboot animation to the launch buttons
2024-10-19 Fix SSID list, implement as HTML5 datalist
2024-10-19 Make reboot button selectors more narrow.
2024-10-20 Add system uptime to UI
2024-10-20 Add status indicator legend
2024-10-20 Improve GUI, disable cancel button in STA mode
2024-10-20 Show cancel button on APSTA mode
2024-10-28 Correctly handle clocks with no GNSS
2024-10-29 Increase priority for dial task to kill off flicker
2024-12-27 Bugfix: Implement mutex to protect HTTP port from concurrent access
2024-12-28 Add option for blanking display on non-confirmed time
2025-03-06 Updated project to work with KiCAD version 9
2025-03-06 Update project to KiCAD v9
2025-06-15 Prepare v8 project for KiCAD version 9
